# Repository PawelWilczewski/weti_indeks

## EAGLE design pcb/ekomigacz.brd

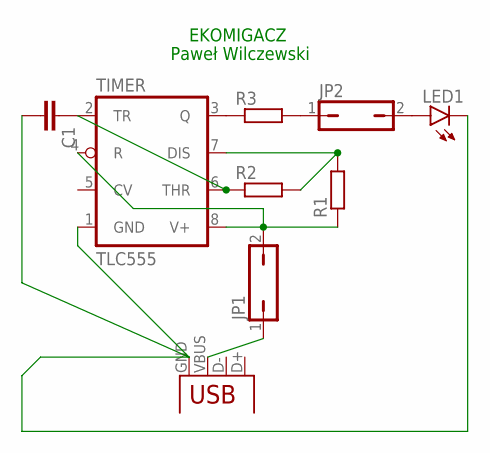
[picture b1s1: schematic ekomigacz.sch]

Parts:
C1: C5/3; C5B3
JP1, JP2: JP1Q; JP1
LED1: LED5MM
R1, R2, R3: R-EU_0207/10; 0207/10
TIMER: TLC555; DIL08
X1: USB-A-H

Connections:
5V: R3.1, TIMER.3 (Q)
unnamed: JP1.1, X1.VBUS
unnamed: R1.2, R2.2, TIMER.7 (DIS)
unnamed: JP1.2, R1.1, TIMER.4 (R), TIMER.8 (V+)
unnamed: C1.1, R2.1, TIMER.2 (TR), TIMER.6 (THR)
unnamed: JP2.1, R3.2
unnamed: JP2.2, LED1.A
unnamed: C1.2, LED1.K (C), TIMER.1 (GND), X1.GND

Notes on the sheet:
EKOMIGACZ
Paweł Wilczewski

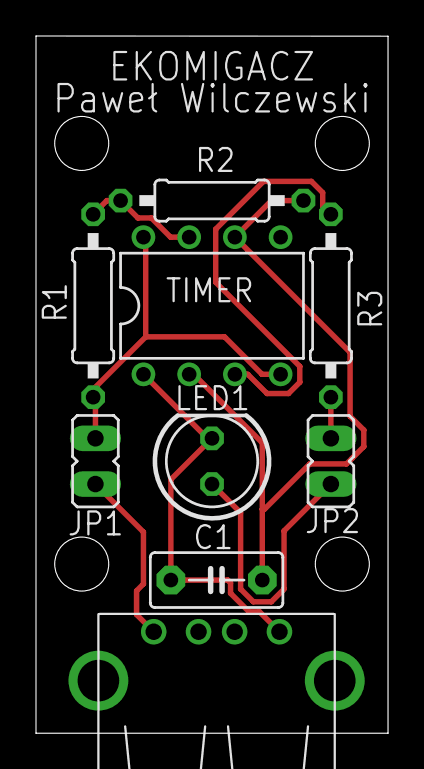
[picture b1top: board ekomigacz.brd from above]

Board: 2 copper layers, 19.6 x 38.7 mm, 9 parts (0 on the bottom side), 8 nets.

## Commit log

2019-03-28 Adding files to repo
2019-04-07 First stage
2019-04-29 model update
2019-05-02 PCB and model update
2019-05-05 final case
2019-06-14 final
2019-06-18 Presentation
2019-06-18 Presentation update
2020-04-24 Small tweaks
